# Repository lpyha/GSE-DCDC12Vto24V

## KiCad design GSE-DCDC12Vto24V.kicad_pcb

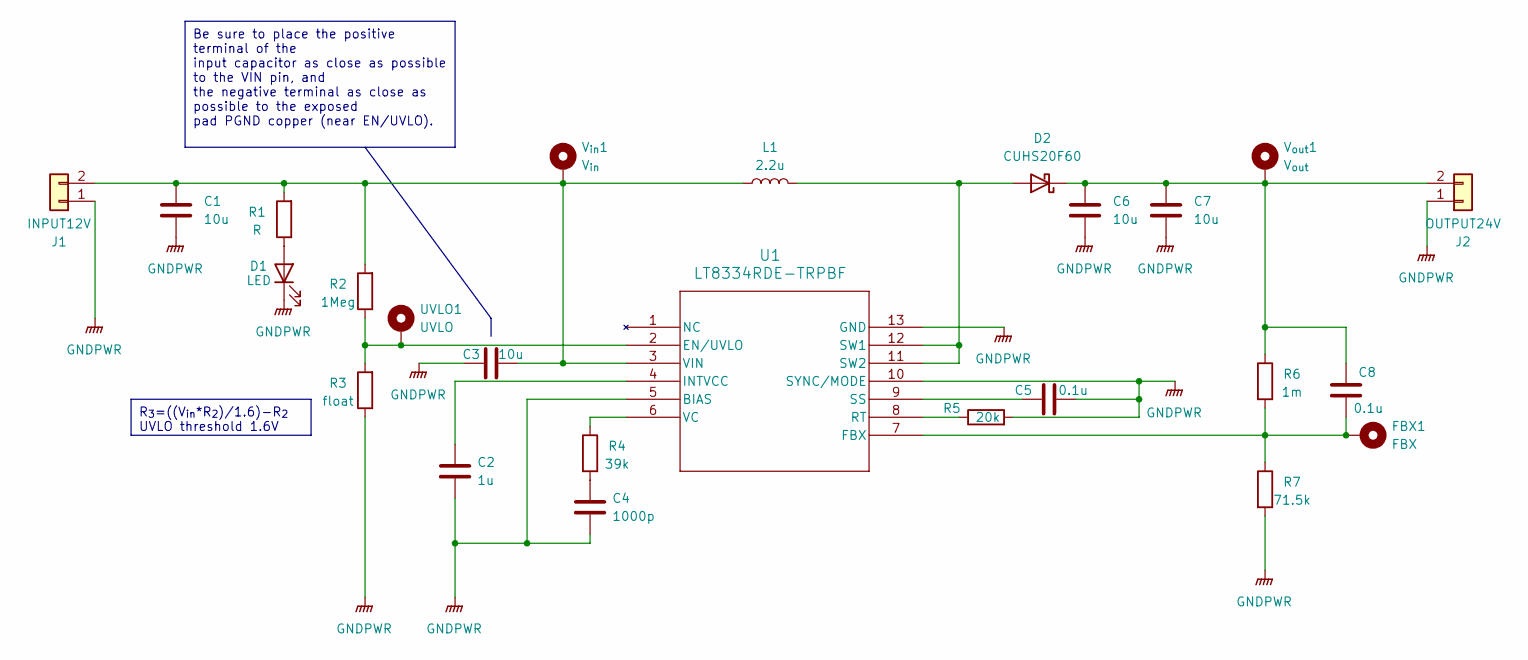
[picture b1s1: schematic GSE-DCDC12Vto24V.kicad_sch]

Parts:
C1, C3, C6, C7: 10u; C_0805_2012Metric_Pad1.18x1.45mm_HandSolder
C2: 1u; C_0603_1608Metric_Pad1.08x0.95mm_HandSolder
C4: 1000p; C_0603_1608Metric_Pad1.08x0.95mm_HandSolder
C5, C8: 0.1u; C_0603_1608Metric_Pad1.08x0.95mm_HandSolder
D1: LED; LED_0603_1608Metric_Pad1.05x0.95mm_HandSolder
D2: CUHS20F60; D_SOD-323_HandSoldering
FBX1: FBX; PinHeader_1x01_P2.54mm_Vertical
J1: INPUT12V; AMASS_XT60PW-M_1x02_P7.20mm_Horizontal
J2: OUTPUT24V; AMASS_XT60PW-F_1x02_P7.20mm_Horizontal
L1: 2.2u; Inductor-wurth
R1: R; R_0603_1608Metric_Pad0.98x0.95mm_HandSolder
R2: 1Meg; R_0603_1608Metric_Pad0.98x0.95mm_HandSolder
R3: float; R_0603_1608Metric_Pad0.98x0.95mm_HandSolder
R4: 39k; R_0603_1608Metric_Pad0.98x0.95mm_HandSolder
R5: 20k; R_0603_1608Metric_Pad0.98x0.95mm_HandSolder
R6: 1m; R_0603_1608Metric_Pad0.98x0.95mm_HandSolder
R7: 71.5k; R_0603_1608Metric_Pad0.98x0.95mm_HandSolder
U1: LT8334RDE-TRPBF; 05-08-1695_ADI
UVLO1: UVLO; PinHeader_1x01_P2.54mm_Vertical
V_{in}1: V_{in}; PinHeader_1x01_P2.54mm_Vertical
V_{out}1: V_{out}; PinHeader_1x01_P2.54mm_Vertical

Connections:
GNDPWR: C1.2, C2.2, C3.2, C4.2, C5.2, C6.2, C7.2, D1.1 (K), J1.1, J2.1, R3.1, R5.2, R7.2, U1.5 (BIAS), U1.10 (SYNC/MODE), U1.13 (GND)
unnamed: C4.1, R4.2
unnamed: D1.2 (A), R1.1
unnamed: D2.2 (A), L1.2, U1.11 (SW2), U1.12 (SW1)
unnamed: C6.1, C7.1, C8.2, D2.1 (K), J2.2, R6.1, V_{out}1.1
unnamed: C1.1, C3.1, J1.2, L1.1, R1.2, R2.2, U1.3 (VIN), V_{in}1.1
unnamed: R2.1, R3.2, U1.2 (EN/UVLO), UVLO1.1
unnamed: C8.1, FBX1.1, R6.2, R7.1, U1.7 (FBX)
unnamed: C2.1, U1.4 (INTVCC)
unnamed: R5.1, U1.8 (RT)
unnamed: C5.1, U1.9 (SS)
unnamed: R4.1, U1.6 (VC)

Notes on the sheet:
Be sure to place the positive terminal of the input capacitor as close as possible to the VIN pin, and the negative terminal as close as possible to the exposed pad PGND copper (near EN/UVLO).
R_{3}=((V_{in}*R_{2})/1.6)-R_{2} UVLO threshold 1.6V

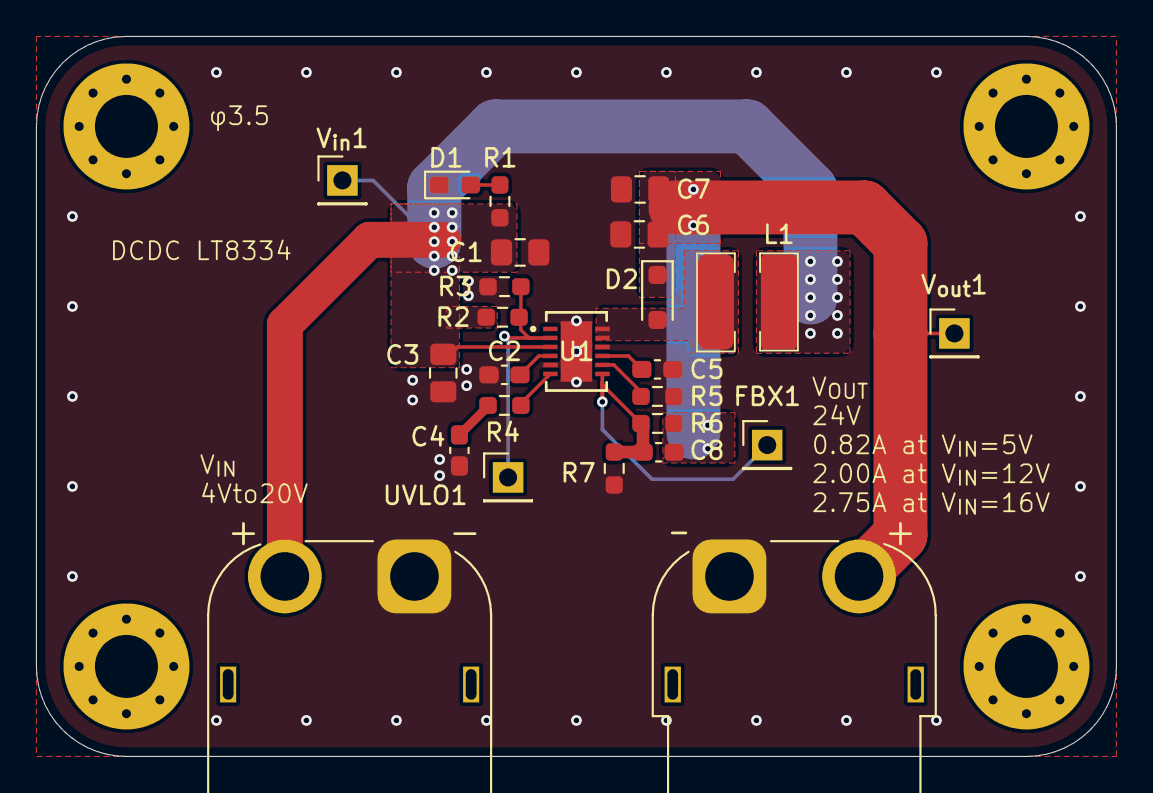
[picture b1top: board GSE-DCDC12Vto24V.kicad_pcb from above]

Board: 2 copper layers, 60.0 x 40.0 mm, 25 parts (0 on the bottom side), 12 nets.

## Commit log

2024-09-18 Add .gitignore, BOM, kicad_prl, and library files
